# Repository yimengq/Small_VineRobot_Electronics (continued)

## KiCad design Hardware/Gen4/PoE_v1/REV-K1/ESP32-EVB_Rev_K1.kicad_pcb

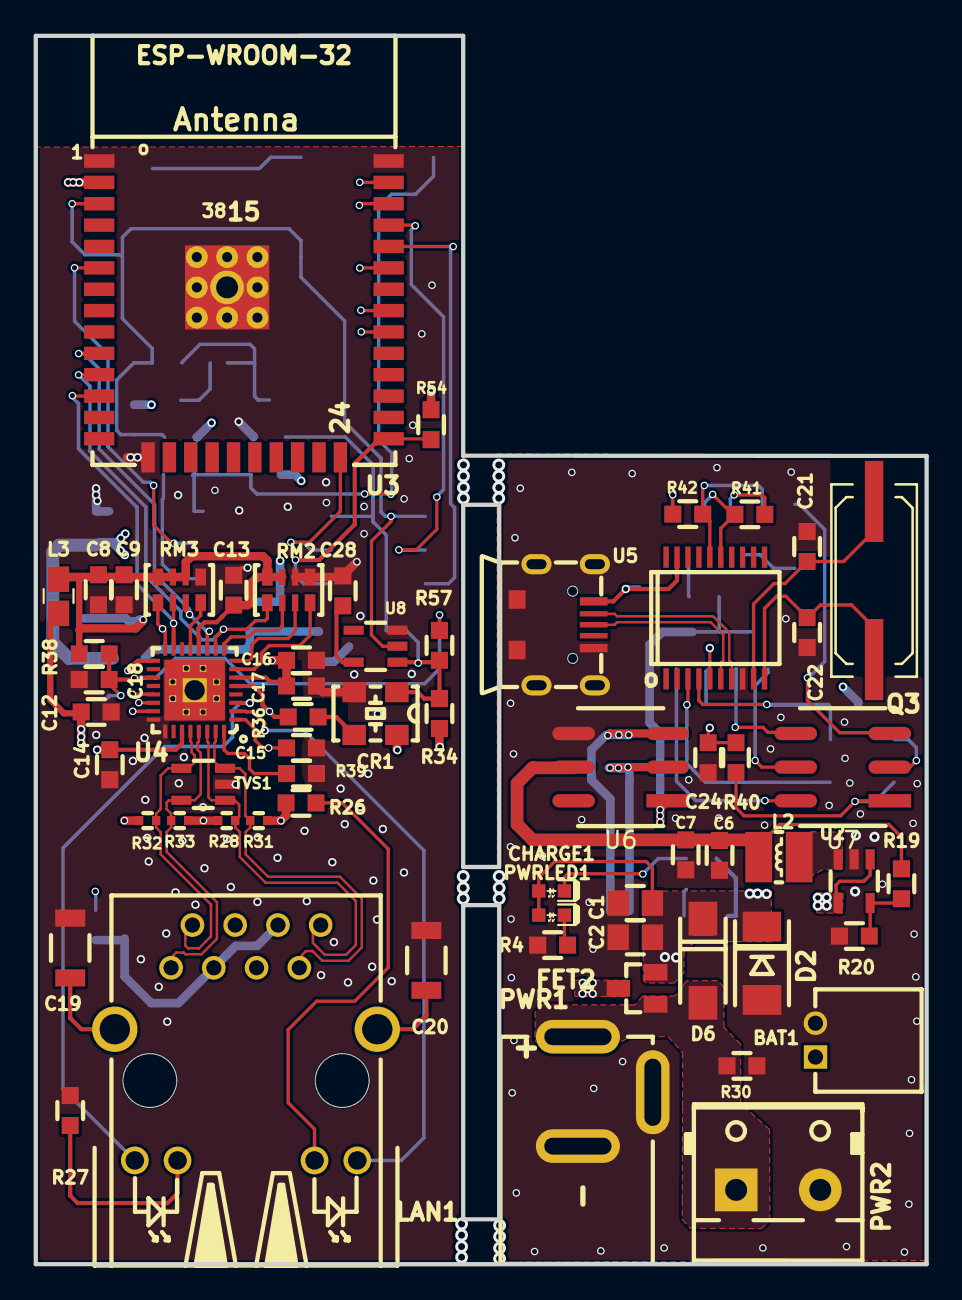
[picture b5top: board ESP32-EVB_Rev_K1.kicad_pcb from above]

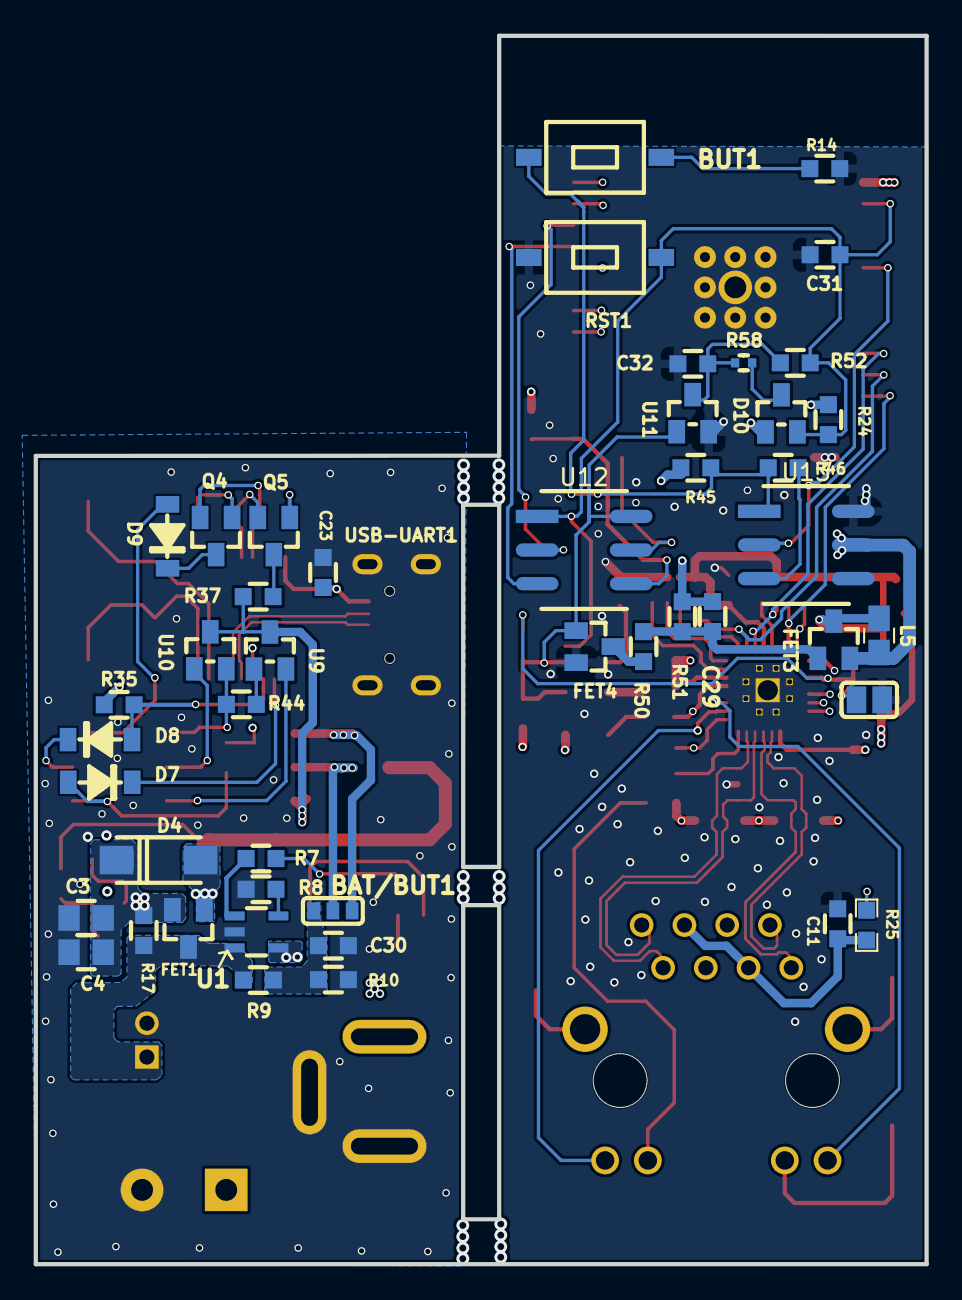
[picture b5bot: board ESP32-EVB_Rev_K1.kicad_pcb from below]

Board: 4 copper layers, 52.9 x 73.0 mm, 108 parts (46 on the bottom side), 82 nets.

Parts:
BAT1: DW02R; LIPO_BAT-CON2DW02R
BAT/BUT1: Opened(2-3)/Soldered(1-2); SJ_2_SMALL
BUT1: T1107A(6x3,8x2,5MM)
C1, C3: NA(47uF/6.3V/20%/X5R/C0805); C_0805_5MIL_DWS
C2, C4: 47uF/6.3V/20%/X5R/C0805; C_0805_5MIL_DWS
C6, C7, C8, C9, C12, C23, C29: 22uF/6.3V/20%/X5R/C0603; C_0603_5MIL_DWS
C11, C13, C14, C15, C17, C24, C30: 100nF/50V/20%/Y5V/C0603; C_0603_5MIL_DWS
C16: 2.2uF/6.3V/10%/X5R/C0603; C_0603_5MIL_DWS
C18: 1nF/50V/5%/NPO(COG)/C0603; C_0603_5MIL_DWS
C19: 1nF/2000V/10%/X7R/C1206; C_1206_5MIL_DWS_ISO
C20: NA(1nF/2000V/10%/X7R/C1206); C_1206_5MIL_DWS_ISO
C21, C22: 27pF/50V/5%/C0G/C0603; C_0603_5MIL_DWS
C28: NA(470nF/16V/10%/X7R/C0603); C_0603_5MIL_DWS
C31, C32: 1uF/10V/10%/X5R/C0603; C_0603_5MIL_DWS
CHARGE1: LED/Yellow/0603; LED_0603_KA
CR1: Q50MHz/25ppm/3V/4P/5x3.2mm; 5032-4P_HCX-3S
D2: SMBJ6.0A(DO-214AA); DO214AA_1(K)-2(A)
D4, D6: 1N5822/SS34/SMA; SMA-KA
D7, D8, D9: 1N5819S4(SOD-123); SOD-123_1C-2A_KA
D10: BAT54A(SOT23-3); SOT23-3
FET1, FET2, FET3: WPM2015-3/TR; SOT23
FET4: BSS138; SOT23
L2: 2.2uH/1.5A/DCR=72mR/20%/3.00x3.00x1.50mm/CD32(NR3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; CD32
L3: FB0805/600R/2A; L_0805_5MIL_DWS
L5: NA(FB0805/600R/2A); L_0805_5MIL_DWS
LAN1: RJLD-060TC1(LPJ4013EDNL); RJLBC-060TC1
PHY_RST1: Opened; SJ
PWR1: PWRJ-2mm(YDJ-1134); PWRJ-2mm(YDJ-1136)
PWR2: NA(TB2 DG306-5.0-2P); TB2-DG306-5.0_2P
PWRLED1: LED/RED/0603; LED_0603_KA
Q3: Q12MHz/20pF/30ppm/2P/HC-49SM(SMD); Q_49U3HMS
Q4, Q5: BC817-40(SOT23); SOT23
R4, R7: 2.2k/R0603; R_0603_5MIL_DWS
R8: 2k/1%/R0603; R_0603_5MIL_DWS
R9, R10: 470k/R0603; R_0603_5MIL_DWS
R14, R26, R27, R37: 220R/R0603; R_0603_5MIL_DWS
R17, R44, R46, R54: NA/R0603; R_0603_5MIL_DWS
R19: 220k/R0603; R_0603_5MIL_DWS
R20: 49.9k/1%/R0603; R_0603_5MIL_DWS
R24, R30, R34, R35, R38, R40, R45, R51: 10k/R0603; R_0603_5MIL_DWS
R25: 0R(board_mounted); 0R_0603
R28, R31, R32, R33, R58: 49.9R/1%/R0402; R_0402_5MIL_DWS
R36: 10R/R0603; R_0603_5MIL_DWS
R39: 12.1k/1%/R0603; R_0603_5MIL_DWS
R41, R42, R50: 1k/R0603; R_0603_5MIL_DWS
R52: 100k/R0603; R_0603_5MIL_DWS
R57: NA(1k/R0603); R_0603_5MIL_DWS
RM2, RM3: RA1206_(4X0603)_4B8_2.2k; R_MATRIX_4
RST1: T1107A(6x3,8x2,5MM)
TVS1: ESDS314DBVR(SOT-23-5); SOT-23-5
U1: BL4054B-42TPRN(SOT23-5); SOT-23-5
U2: SY8089AAAC(SOT23-5); SOT-23-5
U3: ESP-WROOM-32; ESP-WROOM-32_MODULE
U4: LAN8710A-EZC(QFN32); QFN32_EP(33)_5.00x5.00x0.90mm_Pitch_0.50mm
U5: CH340T(SSOP20W); SSOP-20W
U6, U7, U12, U13: 2_3P针座; 2.0MM
U8: NA(NCP303LSN27T1G(SOT-23-5)); SOT-23-5
U9, U10: BAT54C(SOT23-3); SOT23-3
U11: HX7027(SOT-23); SOT-23
USB-UART1: MISB-SWMM-5B-LF(USB_MICRO); USB-MICRO_MISB-SWMM-5B_LF

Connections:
+3.3V: C29.1, CR1.4 (VDD), D10.1 (C1), FET3.2, L5.1, R24.1, R34.1, R45.1, R51.1, R54.2, U3.2 (3V3), U13.4
+3.3VLAN: C8.1, C9.1, C13.1, FET3.3, L3.1, L5.2, R38.2, RM2.3.1, RM2.4.1, RM3.1.2, RM3.2.2, RM3.3.2, U4.12 (VDDIO)
+5V: C1.1, C2.1, CHARGE1.2 (A), D2.1 (K), D4.2 (A), D6.1 (K), FET1.1, FET2.2, PWRLED1.2 (A), U1.4 (VCC)
/+5V_EXT: D6.2 (A), FET2.1, PWR1.+, PWR2.1, R30.1
/+5V_USB: C23.1, FET2.3, R35.1, U5.19 (VCC), USB-UART1.1 (VBUS)
/BUT1: BUT1.1, R45.2, R46.1, U13.1
/C_BUT1: BAT/BUT1.1, U6.5
/C_D_Com: R37.2, U6.1, U9.3 (CC), U10.3 (CC)
/C_ESP_EN: D9.2 (A), U7.5
/C_GPI34/BUT1: BAT/BUT1.2, U6.3
/C_GPIO0/XTAL1/CLKIN: U7.2, U9.2 (A2)
/C_GPIO1/U0TXD: D8.1 (K), U7.3
/C_GPIO2/HS2_DATA0: U7.4, U10.1 (A1)
/C_GPIO3/U0RXD: D7.2 (A), R40.2, U7.1
/C_OSC_DIS: R44.1, U7.6, U10.2 (A2)
/D_Com: R46.2, U13.5
/D_N: U5.7 (UD-), USB-UART1.2 (D-)
/D_P: U5.6 (UD+), USB-UART1.3 (D+)
/ESP_EN: C31.2, D10.2 (C2), R24.2, R52.2, RST1.1, U3.3 (EN), U8.2 (VDD), U12.1
/G: LAN1.AG1 (AG), R26.2
/GPI34/BUT1: U3.6 (GPI34/ADC1_CH6/RTC_GPIO4), U13.3
/GPIO0/XTAL1/CLKIN: R36.2, R54.1, U3.25 (GPIO0/ADC2_CH1/TOUCH1/RTC_GPIO11/CLK_OU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), U4.5 (XTAL1/CLKIN), U12.6
/GPIO1/U0TXD: U3.35 (GPIO1/U0TXD/CLK_OUT3/EMAC_RXD2), U12.3
/GPIO2/HS2_DATA0: U3.24 (GPIO2/ADC2_CH2/TOUCH2/RTC_GPIO12/HSPIWP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), U12.4
/GPIO3/U0RXD: U3.34 (GPIO3/U0RXD/CLK_OUT2), U12.5
/GPIO18/MDIO(RMII): RM3.1.1, U3.30 (GPIO18/VSPICLK/HS1_DATA7), U4.16 (MDIO)
/GPIO19/EMAC_TXD0(RMII): U3.31 (GPIO19/VSPIQ/U0CTS/EMAC_TXD0), U4.22 (TXD0)
/GPIO21/EMAC_TX_EN(RMII): U3.33 (GPIO21/VSPIHD/EMAC_TX_EN), U4.21 (TXEN)
/GPIO22/EMAC_TXD1(RMII): U3.36 (GPIO22/VSPIWP/U0RTS/EMAC_TXD1), U4.23 (TXD1)
/GPIO23/MDC(RMII): U3.37 (GPIO23/VSPID/HS1_STROBE), U4.17 (MDC)
/GPIO25/EMAC_RXD0(RMII): RM3.3.1, U3.10 (GPIO25/DAC_1/ADC2_CH8/RTC_GPIO6/EMAC_RX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), U4.11 (RXD0/MODE0)
/GPIO26/EMAC_RXD1(RMII): RM2.4.2, U3.11 (GPIO26/DAC_2/ADC2_CH9/RTC_GPIO7/EMAC_RX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), U4.10 (RXD1/MODE1)
/GPIO27/EMAC_RX_CRS_DV: RM3.2.1, U3.12 (GPIO27/ADC2_CH7/TOUCH7/RTC_GPIO17/EMAC_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), U4.15 (COL/CRS_DV/MODE2)
/OSC_DIS: CR1.1 (E/D), FET4.1 (G), R34.2, R57.2, U8.1 (#RST), U11.1 (VOut), U12.2
/PHYAD0: RM3.4.1, U4.13 (RXER/RXD4/PHYAD0)
/PHYAD1: RM2.1.2, U4.7 (RXCLK/PHYAD1)
/PHYAD2: RM2.2.2, U4.8 (RXD3/PHYAD2)
/RMIISEL: RM2.3.2, U4.9 (RXD2/RMIISEL)
/RX_N: LAN1.8 (RD-), R28.2, TVS1.1 (I/O1), U4.30 (RXN)
/RX_P: LAN1.7 (RD+), R31.2, TVS1.3 (I/O2), U4.31 (RXP)
/TX_N: LAN1.2 (TD-), R32.2, TVS1.4 (I/O3), U4.28 (TXN)
/TX_P: LAN1.1 (TD+), R33.2, TVS1.5 (I/O4), U4.29 (TXP)
/VDD1A-2A: C12.1, C14.1, C15.1, L3.2, R25.1, R26.1, R28.1, R31.1, R32.1, R33.1, U4.1 (VDD2A), U4.27 (VDD1A)
/VDDCR: C16.1, C17.1, U4.6 (VDDCR)
GND: C8.2, C9.2, C11.2, C12.2, C13.2, C14.2, C15.2, C16.2, C17.2, C18.1, C19.2, C20.2, C28.2, C31.1, C32.1, CR1.2 (VSS), FET4.2 (S), PHY_RST1.1, R14.2, R27.2, R39.2, RM2.1.1, RM2.2.1, RM3.4.2, RST1.2, TVS1.2 (GND), U3.1 (GND), U3.15 (GND), U3.38 (GND), U3.39 (THERMAL_PAD), U4.24 (TXD2), U4.25 (TXD3), U4.33 (GND), U8.3 (GND), U11.2 (Vss), U13.2
unnamed: BAT/BUT1.3, C30.1, R9.2, R10.1
unnamed: BUT1.2, R14.1
unnamed: C19.1, C20.1, LAN1.GND1, LAN1.GND2
unnamed: C29.2, FET3.1, R50.2, R51.2
unnamed: CHARGE1.1 (K), R7.2
unnamed: CR1.3 (OUT), R36.1
unnamed: C3.1, C4.1, D4.1 (K), FET1.2, R17.2, U2.1 (EN), U2.4 (IN)
unnamed: D7.1 (K), U5.3 (TXD)
unnamed: D8.2 (A), R35.2, U5.4 (RXD)
unnamed: D9.1 (K), Q4.3 (C)
unnamed: D10.3 (CA), R58.1
unnamed: FET4.3 (D), R50.1
unnamed: LAN1.AY1 (AY), U4.3 (LED1/REGOFF)
unnamed: C11.1, LAN1.3 (COM), LAN1.6 (NC), R25.2
unnamed: LAN1.KG1 (KG), U4.2 (LED2/NINTSEL)
unnamed: LAN1.KY1 (KY), R27.1
unnamed: PWRLED1.1 (K), R4.1
unnamed: Q4.1 (B), R41.2
unnamed: Q4.2 (E), R42.1, U5.16 (RTS#)
unnamed: Q5.1 (B), R42.2
unnamed: Q5.3 (C), R37.1
unnamed: Q5.2 (E), R41.1, U5.15 (DTR#)
unnamed: R7.1, U1.1 (CHRGb)
unnamed: R8.2, U1.5 (PROG)
unnamed: BAT1.1, FET1.3, R9.1, R17.1, U1.3 (VBAT)
unnamed: R19.1, R20.1, U2.5 (FB)
unnamed: L2.1, U2.3 (LX)
unnamed: C18.2, PHY_RST1.2, R38.1, R57.1, U4.19 (NRST)
unnamed: R39.1, U4.32 (RBIAS)
unnamed: C24.1, R40.1, U5.5 (V3)
unnamed: C21.1, Q3.1, U5.9 (XI)
unnamed: C22.1, Q3.2, U5.10 (XO)
unnamed: C28.1, U8.5 (CT)
unnamed: R44.2, U9.1 (A1)
unnamed: C32.2, R52.1, R58.2, U11.3 (VIn)
PGND: BAT1.2, C1.2, C2.2, C3.2, C4.2, C6.2, C7.2, C21.2, C22.2, C23.2, C24.2, C30.2, D2.2 (A), PWR1.-, PWR2.2, R4.2, R8.1, R10.2, R20.2, R30.2, U1.2 (GND), U2.2 (GND), U5.8 (GND), U6.6, USB-UART1.0, USB-UART1.5 (GND)
P_+3.3V: C6.1, C7.1, L2.2, R19.2, U6.4

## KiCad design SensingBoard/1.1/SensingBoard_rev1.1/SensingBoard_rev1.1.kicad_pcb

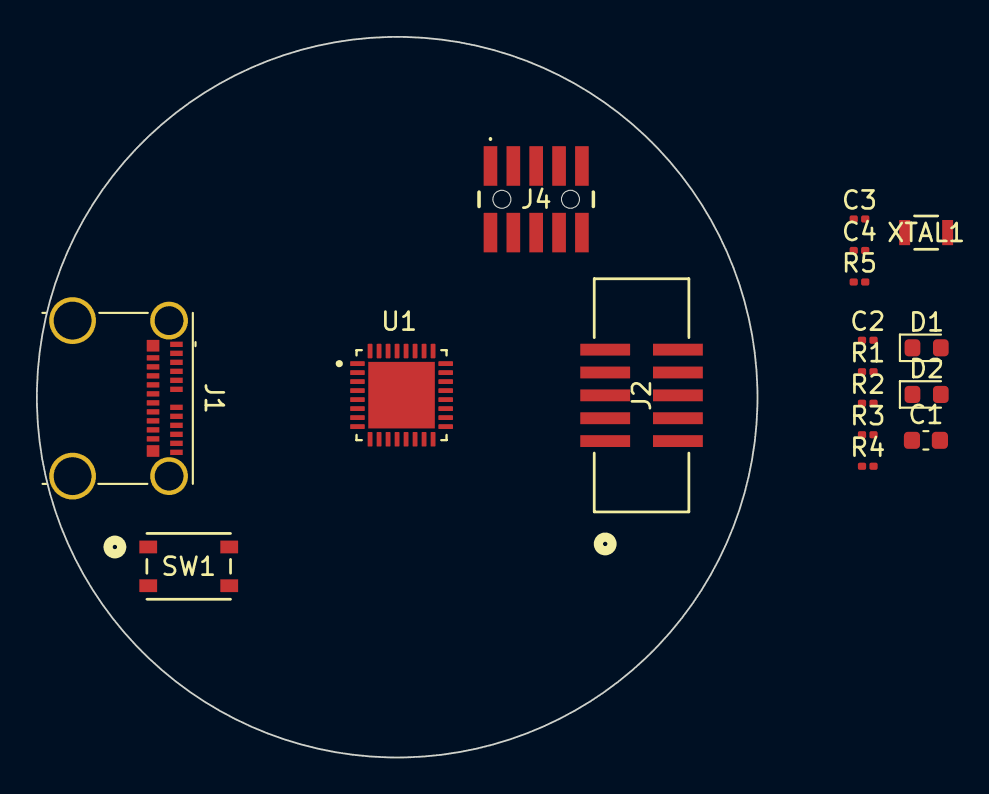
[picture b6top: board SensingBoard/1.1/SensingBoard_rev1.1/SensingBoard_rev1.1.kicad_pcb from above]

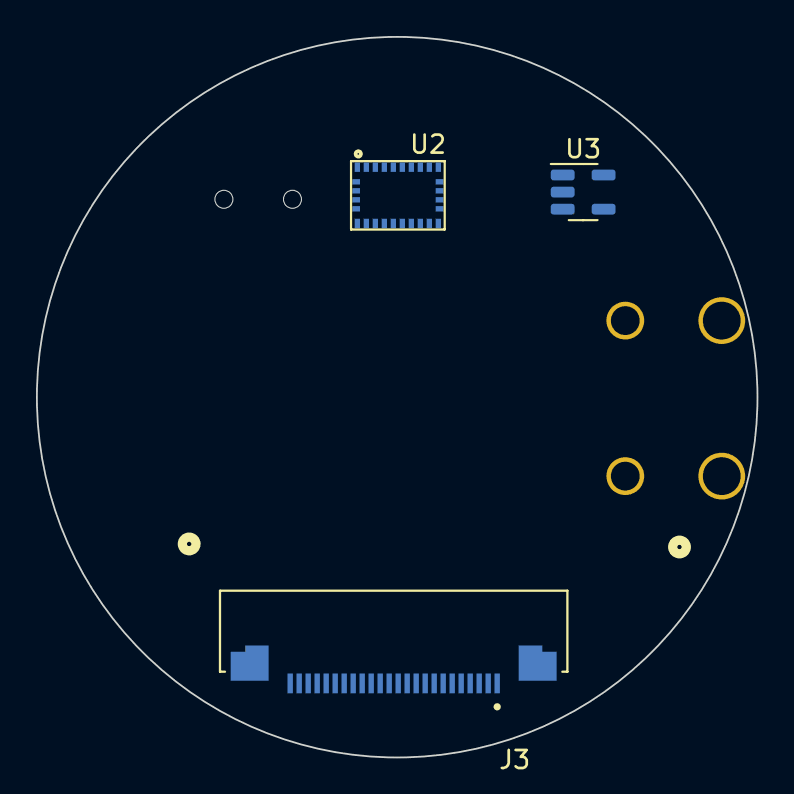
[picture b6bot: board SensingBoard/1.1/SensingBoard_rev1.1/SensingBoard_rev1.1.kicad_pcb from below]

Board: 2 copper layers, 40.0 x 40.0 mm, 20 parts (3 on the bottom side), 20 nets, no tracks yet.

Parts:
C1: 10uF; C_0603_1608Metric
C2: 1uF; C_0201_0603Metric
C3, C4: 22pF; C_0201_0603Metric
D1, D2: LED; LED_0603_1608Metric
J1: USB_C_Receptacle; USB_C_Receptacle_Molex_105450-0101-L
J2: 3221-10-0300-00; CONN10_3221-10-0300-00_CNC
J3: F32R-1A7H1-11024; AMPHENOL_F32R-1A7H1-11024
J4: GRPB052VWQP-RC; GRPB052VWQPRC
R1, R2: 100; R_0201_0603Metric
R3: 6.1K; R_0201_0603Metric
R4: 5.1K; R_0201_0603Metric
R5: 10k; R_0201_0603Metric
SW1: PTS815 SJM 250 SMTR LFS; SW4_PTS815 SJM 250 SMTR LFS_CNK
U1: ESP32C3; QFN32_5X5MM
U2: BNO055; LGA28R50P4X10_380X520X100
U3: MIC5504-3.3YM5; SOT-23-5
XTAL1: ABS07-32.768KHZ-7-T; XTAL_ABS07-32.768KHZ-7-T_ABR

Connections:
+3.3V: C1.2, C2.1, R5.1, U1.2 (VDD3P3), U1.3 (VDD3P3)
D0: J4.2, U1.6 (GPIO2)
D1: J4.4, U1.8 (GPIO3)
D2: J4.6, U1.9 (MTMS)
D3: J4.8, U1.10 (MTDI)
D4: J4.10, U1.12 (MTCK)
D5: J4.1, U1.13 (MTDO)
D8: J4.3, U1.14 (GPIO8)
D9: J4.5, U1.15 (GPIO9)
GND: C3.2, C4.2, J4.7, J4.9, R3.2, R4.2, SW1.4, U1.33 (GND)
unnamed: J1.A5 (CC1), R4.1
unnamed: J1.B5 (CC2), R3.1
unnamed: J1.A1 (GND), J1.A12 (GND), J1.B1 (GND), J1.B12 (GND)
unnamed: R5.2, SW1.2
unnamed: U1.31 (VDDA), U1.32 (VDDA)
unnamed: C4.1, U1.5 (XTAL_32K_N), XTAL1.2
unnamed: C3.1, U1.4 (XTAL_32K_P), XTAL1.1
USB_DN: J1.A7 (D-), J1.B7 (D-), U1.25 (GPIO18)
USB_DP: J1.A6 (D+), J1.B6 (D+), U1.26 (GPIO19)
VBUS: J1.A4 (VBUS), J1.A9 (VBUS), J1.B4 (VBUS), J1.B9 (VBUS)
